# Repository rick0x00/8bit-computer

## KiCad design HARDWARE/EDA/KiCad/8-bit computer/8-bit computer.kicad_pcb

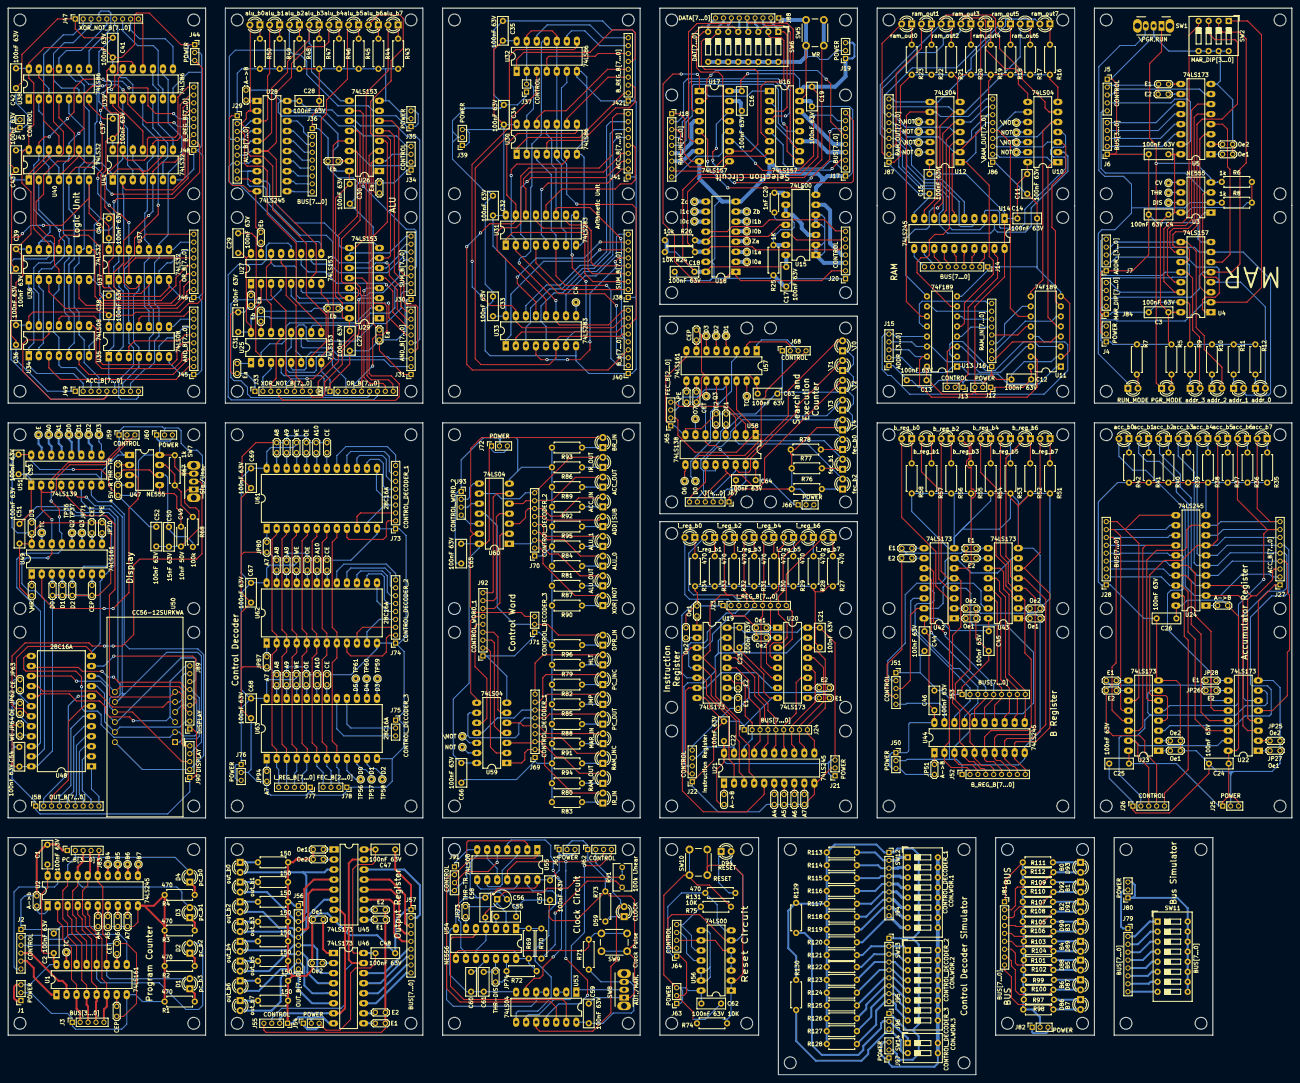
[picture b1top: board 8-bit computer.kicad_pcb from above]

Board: 2 copper layers, 325.0 x 270.0 mm, 601 parts (0 on the bottom side), 106 nets.

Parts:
C1, C2, C3, C4, C5, C11, C12, C13, C14, C15, C16, C17, C18, C19, C21, C22, C23, C24, C25, C26, C27, C28, C29, C30, C31, C32, C33, C34, C35, C36, C37, C38, C39, C40, C41, C42, C43, C44, C45, C46, C47, C48, C51, C52, C53, C54, C57, C58, C59, C62, C63, C64, C65, C66, C67, C68, C69: 100nF 63V; C_Rect_L7.0mm_W2.5mm_P5.00mm
C20: 1nF; C_Disc_D4.3mm_W1.9mm_P5.00mm
C49: 10nF 50V; C_Disc_D4.3mm_W1.9mm_P5.00mm
C50: 15nF 63V; C_Rect_L7.0mm_W2.5mm_P5.00mm
C55, C60: 10nF 63V; C_Rect_L7.0mm_W2.5mm_P5.00mm
C56: 10uF 25V; CP_Radial_Tantal_D4.5mm_P2.50mm
C61: 330nF 63V; C_Rect_L7.0mm_W2.5mm_P5.00mm
D1: pc_b3; LED_D3.0mm
D2: pc_b2; LED_D3.0mm
D3: pc_b1; LED_D3.0mm
D4: pc_b0; LED_D3.0mm
D5: PGR_MODE; LED_D3.0mm
D6: RUN_MODE; LED_D3.0mm
D7: addr_3; LED_D3.0mm
D8: addr_2; LED_D3.0mm
D9: addr_1; LED_D3.0mm
D10: addr_0; LED_D3.0mm
D11: ram_out7; LED_D3.0mm
D12: ram_out6; LED_D3.0mm
D13: ram_out5; LED_D3.0mm
D14: ram_out4; LED_D3.0mm
D15: ram_out3; LED_D3.0mm
D16: ram_out2; LED_D3.0mm
D17: ram_out1; LED_D3.0mm
D18: ram_out0; LED_D3.0mm
D19: i_reg_b7; LED_D3.0mm
D20: i_reg_b6; LED_D3.0mm
D21: i_reg_b5; LED_D3.0mm
D22: i_reg_b4; LED_D3.0mm
D23: i_reg_b3; LED_D3.0mm
D24: i_reg_b2; LED_D3.0mm
D25: i_reg_b1; LED_D3.0mm
D26: i_reg_b0; LED_D3.0mm
D27: acc_b7; LED_D3.0mm
D28: acc_b6; LED_D3.0mm
D29: acc_b5; LED_D3.0mm
D30: acc_b4; LED_D3.0mm
D31: acc_b3; LED_D3.0mm
D32: acc_b2; LED_D3.0mm
D33: acc_b1; LED_D3.0mm
D34: acc_b0; LED_D3.0mm
D35: alu_b7; LED_D3.0mm
D36: alu_b6; LED_D3.0mm
D37: alu_b5; LED_D3.0mm
D38: alu_b4; LED_D3.0mm
D39: alu_b3; LED_D3.0mm
D40: alu_b2; LED_D3.0mm
D41: alu_b1; LED_D3.0mm
D42: alu_b0; LED_D3.0mm
D43: b_reg_b7; LED_D3.0mm
D44: b_reg_b6; LED_D3.0mm
D45: b_reg_b5; LED_D3.0mm
D46: b_reg_b4; LED_D3.0mm
D47: b_reg_b3; LED_D3.0mm
D48: b_reg_b2; LED_D3.0mm
D49: b_reg_b1; LED_D3.0mm
D50: b_reg_b0; LED_D3.0mm
D51: out_b7; LED_D3.0mm_Clear
D52: out_b6; LED_D3.0mm_Clear
D53: out_b5; LED_D3.0mm_Clear
D54: out_b4; LED_D3.0mm_Clear
D55: out_b3; LED_D3.0mm_Clear
D56: out_b2; LED_D3.0mm_Clear
D57: out_b1; LED_D3.0mm_Clear
D58: out_b0; LED_D3.0mm_Clear
D59: CLOCK; LED_D3.0mm
D60: fec_b2; LED_D3.0mm_Clear
D61: fec_b1; LED_D3.0mm_Clear
D62: fec_b0; LED_D3.0mm_Clear
D63: \T4; LED_D3.0mm_Clear
D64: \T3; LED_D3.0mm_Clear
D65: \T2; LED_D3.0mm_Clear
D66: \T1; LED_D3.0mm_Clear
D67: \T0; LED_D3.0mm_Clear
D68: HLT; LED_D3.0mm_Clear
D69: RAM_OUT; LED_D3.0mm_Clear
D70: ALU_0; LED_D3.0mm_Clear
D71: PC_INC; LED_D3.0mm_Clear
D72: IR_IN; LED_D3.0mm_Clear
D73: ALU_1; LED_D3.0mm_Clear
D74: JMP; LED_D3.0mm_Clear
D75: IR_OUT; LED_D3.0mm_Clear
D76: ALU_OUT; LED_D3.0mm_Clear
D77: PC_OUT; LED_D3.0mm_Clear
D78: ACC_OUT; LED_D3.0mm_Clear
D79: XOR|NOT; LED_D3.0mm_Clear
D80: MAR_IN; LED_D3.0mm_Clear
D81: ACC_IN; LED_D3.0mm_Clear
D82: BR_IN; LED_D3.0mm_Clear
D83: RAM_INC; LED_D3.0mm_Clear
D84: ADD|SUB; LED_D3.0mm_Clear
D85: OPR_IN; LED_D3.0mm_Clear
D86: B7; LED_D3.0mm_Clear
D87: B6; LED_D3.0mm_Clear
D88: B5; LED_D3.0mm_Clear
D89: B4; LED_D3.0mm_Clear
D90: B3; LED_D3.0mm_Clear
D91: B2; LED_D3.0mm_Clear
D92: B1; LED_D3.0mm_Clear
D93: B0; LED_D3.0mm_Clear
D94: RESET; LED_D3.0mm
J1, J4, J12, J19, J21, J25, J35, J39, J44, J50, J54, J60, J61, J63, J66, J72, J76, J80, J82, J97: POWER; PinSocket_1x03_P2.00mm_Vertical
J2: CONTROL; PinSocket_1x06_P2.00mm_Vertical
J3, J6: BUS[3...0]; PinSocket_1x05_P2.00mm_Vertical
J5, J22, J26, J51, J64: CONTROL; PinSocket_1x05_P2.00mm_Vertical
J7, J15: ADDR_[3...0]; PinSocket_1x05_P2.00mm_Vertical
J13, J59: CONTROL; PinSocket_1x03_P2.00mm_Vertical
J14, J17, J24, J28, J36, J53, J57, J79, J81: BUS[7...0]; PinSocket_1x09_P2.00mm_Vertical
J16, J18: RAM_IN[7...0]; PinSocket_1x09_P2.00mm_Vertical
J20: CONTROL; PinSocket_1x07_P2.00mm_Vertical
J23: I_REG_B[7...0]; PinSocket_1x09_P2.00mm_Vertical
J27, J41, J49: ACC_B[7...0]; PinSocket_1x09_P2.00mm_Vertical
J29: ALU_B[7...0]; PinSocket_1x09_P2.00mm_Vertical
J30, J38: SUM_B[7...0]; PinSocket_1x09_P2.00mm_Vertical
J31, J45: AND_B[7...0]; PinSocket_1x09_P2.00mm_Vertical
J32, J46: OR_B[7...0]; PinSocket_1x09_P2.00mm_Vertical
J33, J47: XOR_NOT_B[7...0]; PinSocket_1x09_P2.00mm_Vertical
J34, J55, J62, J68, J91: CONTROL; PinSocket_1x04_P2.00mm_Vertical
J37, J43: CONTROL; PinSocket_1x02_P2.00mm_Vertical
J40: B_b[7...0]; PinSocket_1x09_P2.00mm_Vertical
J42, J48, J52: B_REG_B[7...0]; PinSocket_1x09_P2.00mm_Vertical
J56, J58: OUT_B[7...0]; PinSocket_1x09_P2.00mm_Vertical
J65, J78: FEC_B[2...0]; PinSocket_1x04_P2.00mm_Vertical
J67: \T[4...0]; PinSocket_1x06_P2.00mm_Vertical
J69, J73, J94: CONTROL_DECODER_1; PinSocket_1x09_P2.00mm_Vertical
J70, J74, J95: CONTROL_DECODER_2; PinSocket_1x09_P2.00mm_Vertical
J71, J75, J96: CONTROL_DECODER_3; PinSocket_1x03_P2.00mm_Vertical
J77: I_REG_B[7...0]; PinSocket_1x05_P2.00mm_Vertical
J83: PC_B[3...0]; PinSocket_1x05_P2.00mm_Vertical
J84: MAR_DIP[7...0]; PinSocket_1x05_P2.00mm_Vertical
J86: \RAM_OUT[7...0]; PinSocket_1x09_P2.00mm_Vertical
J87: RAM_OUT[7...0]; PinSocket_1x09_P2.00mm_Vertical
J88: DATA[7...0]; PinSocket_1x09_P2.00mm_Vertical
J89: DISPLAY; PinSocket_1x09_P2.00mm_Vertical
J90: DISPLAY; PinSocket_1x05_P2.00mm_Vertical
J92: CONTROL_WORD_1; PinSocket_1x09_P2.00mm_Vertical
J93: CONTROL_WORD_2; PinSocket_1x04_P2.00mm_Vertical
JP1, JP20: A4; TestPoint_2Pads_Pitch2.54mm_Drill0.8mm
JP2, JP21: A5; TestPoint_2Pads_Pitch2.54mm_Drill0.8mm
JP3, JP22: A6; TestPoint_2Pads_Pitch2.54mm_Drill0.8mm
JP4, JP23, JP80, JP87, JP94: A7; TestPoint_2Pads_Pitch2.54mm_Drill0.8mm
JP5: A->b; TestPoint_2Pads_Pitch2.54mm_Drill0.8mm
JP6, JP71, JP77: CET; TestPoint_2Pads_Pitch2.54mm_Drill0.8mm
JP7, JP67, JP75: CEP; TestPoint_2Pads_Pitch2.54mm_Drill0.8mm
JP8, JP14, JP18, JP27, JP31, JP45, JP49, JP56, JP58: Oe1; TestPoint_2Pads_Pitch2.54mm_Drill0.8mm
JP9, JP13, JP17, JP26, JP30, JP44, JP48, JP53, JP55, JP78: E2; TestPoint_2Pads_Pitch2.54mm_Drill0.8mm
JP10, JP12, JP16, JP25, JP29, JP43, JP47, JP52, JP54: Oe2; TestPoint_2Pads_Pitch2.54mm_Drill0.8mm
JP11, JP15, JP19, JP28, JP32, JP46, JP50, JP57, JP59, JP79: E1; TestPoint_2Pads_Pitch2.54mm_Drill0.8mm
JP24, JP33, JP40, JP51: A->B; TestPoint_2Pads_Pitch2.54mm_Drill0.8mm
JP34, JP36, JP38, JP41: Ea; TestPoint_2Pads_Pitch2.54mm_Drill0.8mm
JP35, JP37, JP39, JP42: Eb; TestPoint_2Pads_Pitch2.54mm_Drill0.8mm
JP60: +5V-R; TestPoint_2Pads_Pitch2.54mm_Drill0.8mm
JP61, JP73: THR-TR; TestPoint_2Pads_Pitch2.54mm_Drill0.8mm
JP62, JP85, JP92, JP99: OE; TestPoint_2Pads_Pitch2.54mm_Drill0.8mm
JP63, JP84, JP91, JP98: CE; TestPoint_2Pads_Pitch2.54mm_Drill0.8mm
JP64, JP86, JP93, JP100: WE; TestPoint_2Pads_Pitch2.54mm_Drill0.8mm
JP65: D0; TestPoint_2Pads_Pitch2.54mm_Drill0.8mm
JP66: D2; TestPoint_2Pads_Pitch2.54mm_Drill0.8mm
JP68: D1; TestPoint_2Pads_Pitch2.54mm_Drill0.8mm
JP69: D3; TestPoint_2Pads_Pitch2.54mm_Drill0.8mm
JP70, JP76: \PE; TestPoint_2Pads_Pitch2.54mm_Drill0.8mm
JP72: \MR; TestPoint_2Pads_Pitch2.54mm_Drill0.8mm
JP74: THR-DIS; TestPoint_2Pads_Pitch2.54mm_Drill0.8mm
JP81, JP88, JP95: A8; TestPoint_2Pads_Pitch2.54mm_Drill0.8mm
JP82, JP89, JP96: A9; TestPoint_2Pads_Pitch2.54mm_Drill0.8mm
JP83, JP90, JP97: A10; TestPoint_2Pads_Pitch2.54mm_Drill0.8mm
R1, R2, R3, R4, R5, R7, R16, R17, R18, R19, R20, R21, R22, R23, R27, R28, R29, R30, R31, R32, R33, R34, R35, R36, R37, R38, R39, R40, R41, R42, R43, R44, R45, R46, R47, R48, R49, R50, R51, R52, R53, R54, R55, R56, R57, R58, R73, R131: 470; R_Axial_DIN0207_L6.3mm_D2.5mm_P7.62mm_Horizontal
R6, R8, R67: 1k; R_Axial_DIN0207_L6.3mm_D2.5mm_P7.62mm_Horizontal
R9, R10, R11, R12, R59, R60, R61, R62, R63, R64, R65, R66, R69: 150; R_Axial_DIN0207_L6.3mm_D2.5mm_P7.62mm_Horizontal
R24, R74, R75: 10K; R_Axial_DIN0207_L6.3mm_D2.5mm_P7.62mm_Horizontal
R25, R98, R100, R102, R104, R106, R108, R110, R112: 1K; R_Axial_DIN0207_L6.3mm_D2.5mm_P7.62mm_Horizontal
R26, R71, R97, R99, R101, R103, R105, R107, R109, R111, R113, R114, R115, R116, R117, R118, R119, R120, R121, R122, R123, R124, R125, R126, R127, R128, R129, R130: 10k; R_Axial_DIN0207_L6.3mm_D2.5mm_P7.62mm_Horizontal
R68: 100k; R_Axial_DIN0207_L6.3mm_D2.5mm_P7.62mm_Horizontal
R70: 10; R_Axial_DIN0207_L6.3mm_D2.5mm_P7.62mm_Horizontal
R72: 330k; R_Axial_DIN0207_L6.3mm_D2.5mm_P7.62mm_Horizontal
R76, R77, R78: 330; R_Axial_DIN0207_L6.3mm_D2.5mm_P7.62mm_Horizontal
R79, R80, R81, R82, R83, R84, R85, R86, R87, R88, R89, R90, R91, R92, R93, R94, R95, R96: 3K; R_Axial_DIN0207_L6.3mm_D2.5mm_P7.62mm_Horizontal
RV1: 100k Linear; Potentiometer_Bourns_3266Y_Vertical
SW1: \PGR,RUN; SW_CuK_OS102011MA1QN1_SPDT_Angled
SW2: MAR_DIP[3...0]; SW_DIP_SPSTx04_Slide_9.78x12.34mm_W7.62mm_P2.54mm
SW5: WR; SW_PUSH_6mm_H5mm
SW6: DAT[7...0]; SW_DIP_SPSTx08_Slide_9.78x22.5mm_W7.62mm_P2.54mm
SW7: Sig./Uns.; SW_CuK_OS102011MA1QN1_SPDT_Angled
SW8: AUT./MAN.; SW_CuK_OS102011MA1QN1_SPDT_Angled
SW9: Clock Pulse; SW_PUSH_6mm_H5mm
SW10: RESET; SW_PUSH_6mm_H5mm
SW11: BUS[7...0]; SW_DIP_SPSTx08_Slide_9.78x22.5mm_W7.62mm_P2.54mm
SW12: CON.WOR.1; SW_DIP_SPSTx08_Slide_9.78x22.5mm_W7.62mm_P2.54mm
SW13: CON.WOR.2; SW_DIP_SPSTx08_Slide_9.78x22.5mm_W7.62mm_P2.54mm
SW14: CON.WOR.3; SW_DIP_SPSTx02_Slide_9.78x7.26mm_W7.62mm_P2.54mm
TP1: B4; TestPoint_THTPad_D1.5mm_Drill0.7mm
TP2: B5; TestPoint_THTPad_D1.5mm_Drill0.7mm
TP3: B6; TestPoint_THTPad_D1.5mm_Drill0.7mm
TP4: B7; TestPoint_THTPad_D1.5mm_Drill0.7mm
TP5, TP38, TP51: TC; TestPoint_THTPad_D1.5mm_Drill0.7mm
TP6: CV; TestPoint_THTPad_D1.5mm_Drill0.7mm
TP7: DIS; TestPoint_THTPad_D1.5mm_Drill0.7mm
TP8: THR; TestPoint_THTPad_D1.5mm_Drill0.7mm
TP18, TP19, TP22, TP23, TP54: NOT; TestPoint_THTPad_D1.5mm_Drill0.7mm
TP20, TP21, TP24, TP25, TP55: \NOT; TestPoint_THTPad_D1.5mm_Drill0.7mm
TP26: I0a; TestPoint_THTPad_D1.5mm_Drill0.7mm
TP27: I1a; TestPoint_THTPad_D1.5mm_Drill0.7mm
TP28: I0b; TestPoint_THTPad_D1.5mm_Drill0.7mm
TP29: I1b; TestPoint_THTPad_D1.5mm_Drill0.7mm
TP30: I0c; TestPoint_THTPad_D1.5mm_Drill0.7mm
TP31: I1c; TestPoint_THTPad_D1.5mm_Drill0.7mm
TP32: Za; TestPoint_THTPad_D1.5mm_Drill0.7mm
TP33: Zb; TestPoint_THTPad_D1.5mm_Drill0.7mm
TP34: Zc; TestPoint_THTPad_D1.5mm_Drill0.7mm
TP35: C4; TestPoint_THTPad_D1.5mm_Drill0.7mm
TP36: Q2; TestPoint_THTPad_D1.5mm_Drill0.7mm
TP37, TP50: Q3; TestPoint_THTPad_D1.5mm_Drill0.7mm
TP39: A1; TestPoint_THTPad_D1.5mm_Drill0.7mm
TP40: A0; TestPoint_THTPad_D1.5mm_Drill0.7mm
TP41: E; TestPoint_THTPad_D1.5mm_Drill0.7mm
TP42: O0; TestPoint_THTPad_D1.5mm_Drill0.7mm
TP43: O1; TestPoint_THTPad_D1.5mm_Drill0.7mm
TP44: O2; TestPoint_THTPad_D1.5mm_Drill0.7mm
TP45: O3; TestPoint_THTPad_D1.5mm_Drill0.7mm
TP46, TP56: D0; TestPoint_THTPad_D1.5mm_Drill0.7mm
TP47, TP57: D1; TestPoint_THTPad_D1.5mm_Drill0.7mm
TP48, TP58: D2; TestPoint_THTPad_D1.5mm_Drill0.7mm
TP49, TP59: D3; TestPoint_THTPad_D1.5mm_Drill0.7mm
TP52: O6; TestPoint_THTPad_D1.5mm_Drill0.7mm
TP53: O7; TestPoint_THTPad_D1.5mm_Drill0.7mm
TP60: D4; TestPoint_THTPad_D1.5mm_Drill0.7mm
TP61: D5; TestPoint_THTPad_D1.5mm_Drill0.7mm
U1, U49, U57: 74LS161; DIP-16_W7.62mm_LongPads
U2, U14, U21, U24, U28, U44: 74LS245; DIP-20_W7.62mm_LongPads
U3, U47: NE555; DIP-8_W7.62mm_LongPads
U4, U16, U17, U18: 74LS157; DIP-16_W7.62mm_LongPads
U5, U19, U20, U22, U23, U42, U43, U45, U46: 74LS173; DIP-16_W7.62mm_LongPads
U10, U12, U53, U59, U60: 74LS04; DIP-14_W7.62mm_LongPads
U11, U13: 74F189; DIP-16_W7.62mm
U15, U55, U56: 74LS00; DIP-14_W7.62mm_LongPads
U25, U26, U27, U29: 74LS153; DIP-16_W7.62mm_LongPads
U30, U32, U38, U39: 74LS86; DIP-14_W7.62mm_LongPads
U31, U33: 74LS283; DIP-16_W7.62mm_LongPads
U34, U35: 74LS08; DIP-14_W7.62mm_LongPads
U36, U37, U40, U41: 74LS32; DIP-14_W7.62mm_LongPads
U48, U61, U62, U63: 28C16A; DIP-24_W15.24mm_LongPads
U50: CC56-12SURKWA; CA56-12SURKWA
U51: 74LS139; DIP-16_W7.62mm_LongPads
U54: NE556; DIP-14_W7.62mm_LongPads
U58: 74LS138; DIP-16_W7.62mm_LongPads

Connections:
+5V: C11.1, C12.1, C13.1, C14.1, C15.1, C51.1, C52.1, C53.1, C54.1, J12.1, J12.3, J60.1, J60.3, JP60.2, JP64.1, JP65.1, JP66.1, JP67.1, JP68.1, JP69.1, JP70.1, JP71.1, JP72.1, R67.1, SW7.3, U10.14, U11.16, U12.14, U13.16, U14.1, U14.20, U47.8, U48.24, U49.16, U51.16
/\ram_out0: J86.2, U10.1, U11.5
/\ram_out1: J86.3, U10.3, U11.7
/\ram_out2: J86.4, U10.5, U11.9
/\ram_out3: J86.5, U10.9, U11.11
/\ram_out4: J86.6, U12.1, U13.5
/\ram_out5: J86.7, U12.3, U13.7
/\ram_out6: J86.8, U12.5, U13.9
/\ram_out7: J86.9, U12.9, U13.11
/display_seg_a: J89.2, U48.9, U50.11
/display_seg_b: J89.3, U48.10, U50.7
/display_seg_c: J89.4, U48.11, U50.4
/display_seg_d: J89.5, U48.13, U50.2
/display_seg_dpx: J89.9, U48.17, U50.3
/display_seg_e: J89.6, U48.14, U50.1
/display_seg_f: J89.7, U48.15, U50.10
/display_seg_g: J89.8, U48.16, U50.5
/dp1: J90.2, U50.12, U51.7
/dp2: J90.3, U50.9, U51.6
/dp3: J90.4, U50.8, U51.5
/dp4: J90.5, U50.6, U51.4
/ram_out0: D18.2, J87.2, U10.2, U14.2
/ram_out1: D17.2, J87.3, U10.4, U14.3
/ram_out2: D16.2, J87.4, U10.6, U14.4
/ram_out3: D15.2, J87.5, U10.8, U14.5
/ram_out4: D14.2, J87.6, U12.2, U14.6
/ram_out5: D13.2, J87.7, U12.4, U14.7
/ram_out6: D12.2, J87.8, U12.6, U14.8
/ram_out7: D11.2, J87.9, U12.8, U14.9
GND: C11.2, C12.2, C13.2, C14.2, C15.2, C49.2, C50.2, C51.2, C52.2, C53.2, C54.2, J12.2, J13.1, J14.1, J15.1, J16.1, J58.1, J59.1, J60.2, J86.1, J87.1, J89.1, J90.1, JP62.1, JP63.1, R16.2, R17.2, R18.2, R19.2, R20.2, R21.2, R22.2, R23.2, SW7.1, U10.7, U11.2, U11.8, U12.7, U13.2, U13.8, U14.10, U47.1, U48.12, U49.8, U51.1, U51.8
unnamed: C49.1, U47.5
unnamed: C50.1, JP61.2, R68.2, U47.6
unnamed: D11.1, R16.1
unnamed: D12.1, R17.1
unnamed: D13.1, R18.1
unnamed: D14.1, R19.1
unnamed: D15.1, R20.1
unnamed: D16.1, R21.1
unnamed: D17.1, R22.1
unnamed: D18.1, R23.1
unnamed: JP60.1, U47.4
unnamed: JP61.1, U47.2
unnamed: JP62.2, U48.20
unnamed: JP63.2, U48.18
unnamed: JP64.2, U48.21
unnamed: JP65.2, U49.3
unnamed: JP66.2, U49.5
unnamed: JP67.2, U49.7
unnamed: JP68.2, U49.4
unnamed: JP69.2, U49.6
unnamed: JP70.2, U49.9
unnamed: JP71.2, U49.10
unnamed: JP72.2, U49.1
unnamed: R67.2, R68.1, U47.7
unnamed: SW7.2, U48.19
unnamed: TP18.1, U10.11
unnamed: TP19.1, U10.13
unnamed: TP20.1, U10.10
unnamed: TP21.1, U10.12
unnamed: TP22.1, U12.11
unnamed: TP23.1, U12.13
unnamed: TP24.1, U12.10
unnamed: TP25.1, U12.12
unnamed: TP36.1, U49.12
unnamed: TP37.1, U49.11
unnamed: TP38.1, U49.15
unnamed: TP39.1, U51.13
unnamed: TP40.1, U51.14
unnamed: TP41.1, U51.15
unnamed: TP42.1, U51.12
unnamed: TP43.1, U51.11
unnamed: TP44.1, U51.10
unnamed: TP45.1, U51.9
unnamed: U47.3, U49.2
\RAM_OUT: J13.2, U14.19
\WE: J13.3, U11.3, U13.3
addr_0: J15.2, U11.1, U13.1
addr_1: J15.3, U11.15, U13.15
addr_2: J15.4, U11.14, U13.14
addr_3: J15.5, U11.13, U13.13
bus0: J14.2, U14.18
bus1: J14.3, U14.17
bus2: J14.4, U14.16
bus3: J14.5, U14.15
bus4: J14.6, U14.14
bus5: J14.7, U14.13
bus6: J14.8, U14.12
bus7: J14.9, U14.11
ctnH: J59.2, U48.22, U49.13, U51.3
ctnL: J59.3, U48.23, U49.14, U51.2
out_b0: J58.2, U48.8
out_b1: J58.3, U48.7
out_b2: J58.4, U48.6
out_b3: J58.5, U48.5
out_b4: J58.6, U48.4
out_b5: J58.7, U48.3
out_b6: J58.8, U48.2
out_b7: J58.9, U48.1
ram_in0: J16.2, U11.4
ram_in1: J16.3, U11.6
ram_in2: J16.4, U11.10
ram_in3: J16.5, U11.12
ram_in4: J16.6, U13.4
ram_in5: J16.7, U13.6
ram_in6: J16.8, U13.10
ram_in7: J16.9, U13.12

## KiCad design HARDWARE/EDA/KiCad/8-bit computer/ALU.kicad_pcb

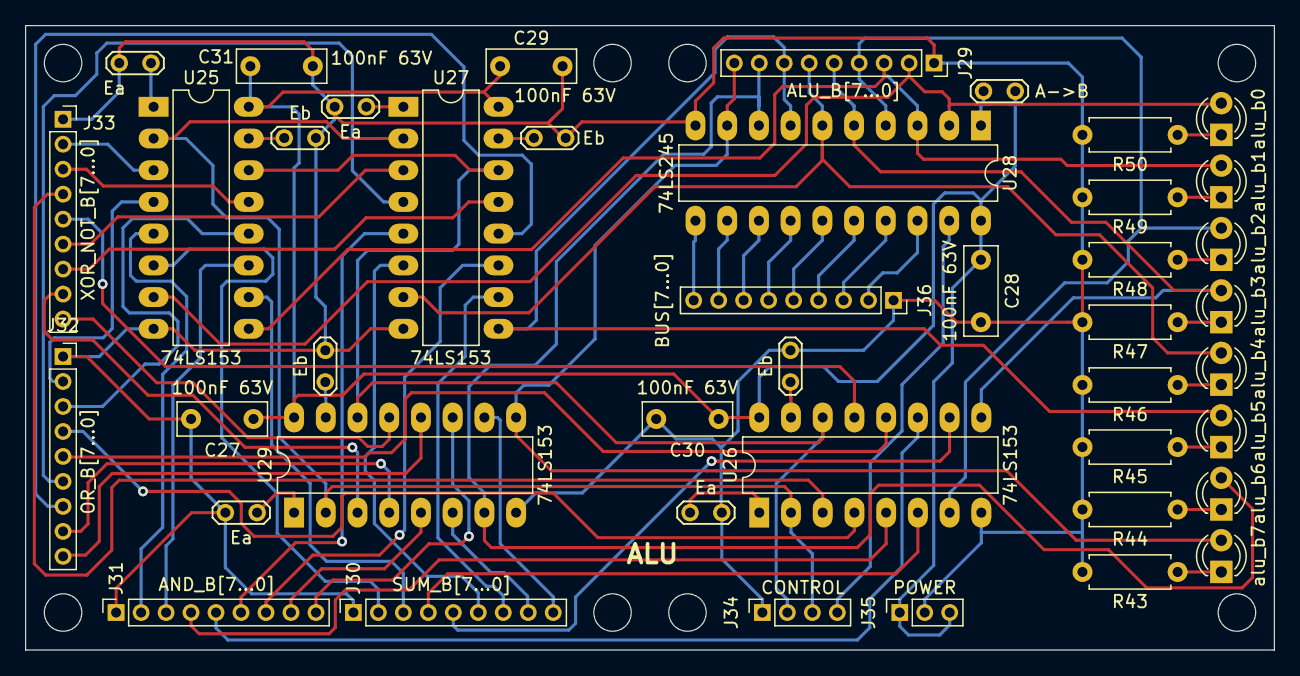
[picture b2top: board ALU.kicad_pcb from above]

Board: 2 copper layers, 100.0 x 50.0 mm, 43 parts (0 on the bottom side), 70 nets.

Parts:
C27, C28, C29, C30, C31: 100nF 63V; C_Rect_L7.0mm_W2.5mm_P5.00mm
D35: alu_b7; LED_D3.0mm
D36: alu_b6; LED_D3.0mm
D37: alu_b5; LED_D3.0mm
D38: alu_b4; LED_D3.0mm
D39: alu_b3; LED_D3.0mm
D40: alu_b2; LED_D3.0mm
D41: alu_b1; LED_D3.0mm
D42: alu_b0; LED_D3.0mm
J29: ALU_B[7...0]; PinSocket_1x09_P2.00mm_Vertical
J30: SUM_B[7...0]; PinSocket_1x09_P2.00mm_Vertical
J31: AND_B[7...0]; PinSocket_1x09_P2.00mm_Vertical
J32: OR_B[7...0]; PinSocket_1x09_P2.00mm_Vertical
J33: XOR_NOT_B[7...0]; PinSocket_1x09_P2.00mm_Vertical
J34: CONTROL; PinSocket_1x04_P2.00mm_Vertical
J35: POWER; PinSocket_1x03_P2.00mm_Vertical
J36: BUS[7...0]; PinSocket_1x09_P2.00mm_Vertical
JP34, JP36, JP38, JP41: Ea; TestPoint_2Pads_Pitch2.54mm_Drill0.8mm
JP35, JP37, JP39, JP42: Eb; TestPoint_2Pads_Pitch2.54mm_Drill0.8mm
JP40: A->B; TestPoint_2Pads_Pitch2.54mm_Drill0.8mm
R43, R44, R45, R46, R47, R48, R49, R50: 470; R_Axial_DIN0207_L6.3mm_D2.5mm_P7.62mm_Horizontal
U25, U26, U27, U29: 74LS153; DIP-16_W7.62mm_LongPads
U28: 74LS245; DIP-20_W7.62mm_LongPads

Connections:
+5V: C27.1, C28.1, C29.1, C30.1, C31.1, J35.1, J35.3, JP40.1, U25.16, U26.16, U27.16, U28.20, U29.16
ALU_0: J34.2, U25.14, U26.14, U27.14, U29.14
ALU_1: J34.3, U25.2, U26.2, U27.2, U29.2
GND: C27.2, C28.2, C29.2, C30.2, C31.2, J29.1, J30.1, J31.1, J32.1, J33.1, J34.1, J35.2, J36.1, JP34.1, JP35.1, JP36.1, JP37.1, JP38.1, JP39.1, JP41.1, JP42.1, R43.2, R44.2, R45.2, R46.2, R47.2, R48.2, R49.2, R50.2, U25.8, U26.8, U27.8, U28.10, U29.8
unnamed: D35.1, R43.1
unnamed: D36.1, R44.1
unnamed: D37.1, R45.1
unnamed: D38.1, R46.1
unnamed: D39.1, R47.1
unnamed: D40.1, R48.1
unnamed: D41.1, R49.1
unnamed: D42.1, R50.1
unnamed: JP34.2, U25.1
unnamed: JP35.2, U25.15
unnamed: JP36.2, U26.1
unnamed: JP37.2, U26.15
unnamed: JP38.2, U27.1
unnamed: JP39.2, U27.15
unnamed: JP40.2, U28.1
unnamed: JP41.2, U29.1
unnamed: JP42.2, U29.15
\ALU_OUT: J34.4, U28.19
alu_b0: D42.2, J29.2, U25.7, U28.2
alu_b1: D41.2, J29.3, U25.9, U28.3
alu_b2: D40.2, J29.4, U26.7, U28.4
alu_b3: D39.2, J29.5, U26.9, U28.5
alu_b4: D38.2, J29.6, U27.7, U28.6
alu_b5: D37.2, J29.7, U27.9, U28.7
alu_b6: D36.2, J29.8, U28.8, U29.7
alu_b7: D35.2, J29.9, U28.9, U29.9
and_b0: J31.2, U25.5
and_b1: J31.3, U25.11
and_b2: J31.4, U26.5
and_b3: J31.5, U26.11
and_b4: J31.6, U27.5
and_b5: J31.7, U27.11
and_b6: J31.8, U29.5
and_b7: J31.9, U29.11
bus0: J36.2, U28.18
bus1: J36.3, U28.17
bus2: J36.4, U28.16
bus3: J36.5, U28.15
bus4: J36.6, U28.14
bus5: J36.7, U28.13
bus6: J36.8, U28.12
bus7: J36.9, U28.11
or_b0: J32.2, U25.4
or_b1: J32.3, U25.12
or_b2: J32.4, U26.4
or_b3: J32.5, U26.12
or_b4: J32.6, U27.4
or_b5: J32.7, U27.12
or_b6: J32.8, U29.4
or_b7: J32.9, U29.12
sum_b0: J30.2, U25.6
sum_b1: J30.3, U25.10
sum_b2: J30.4, U26.6
sum_b3: J30.5, U26.10
sum_b4: J30.6, U27.6
sum_b5: J30.7, U27.10
sum_b6: J30.8, U29.6
sum_b7: J30.9, U29.10
xor_not_b0: J33.2, U25.3
xor_not_b1: J33.3, U25.13
xor_not_b2: J33.4, U26.3
xor_not_b3: J33.5, U26.13
xor_not_b4: J33.6, U27.3
xor_not_b5: J33.7, U27.13
xor_not_b6: J33.8, U29.3
xor_not_b7: J33.9, U29.13

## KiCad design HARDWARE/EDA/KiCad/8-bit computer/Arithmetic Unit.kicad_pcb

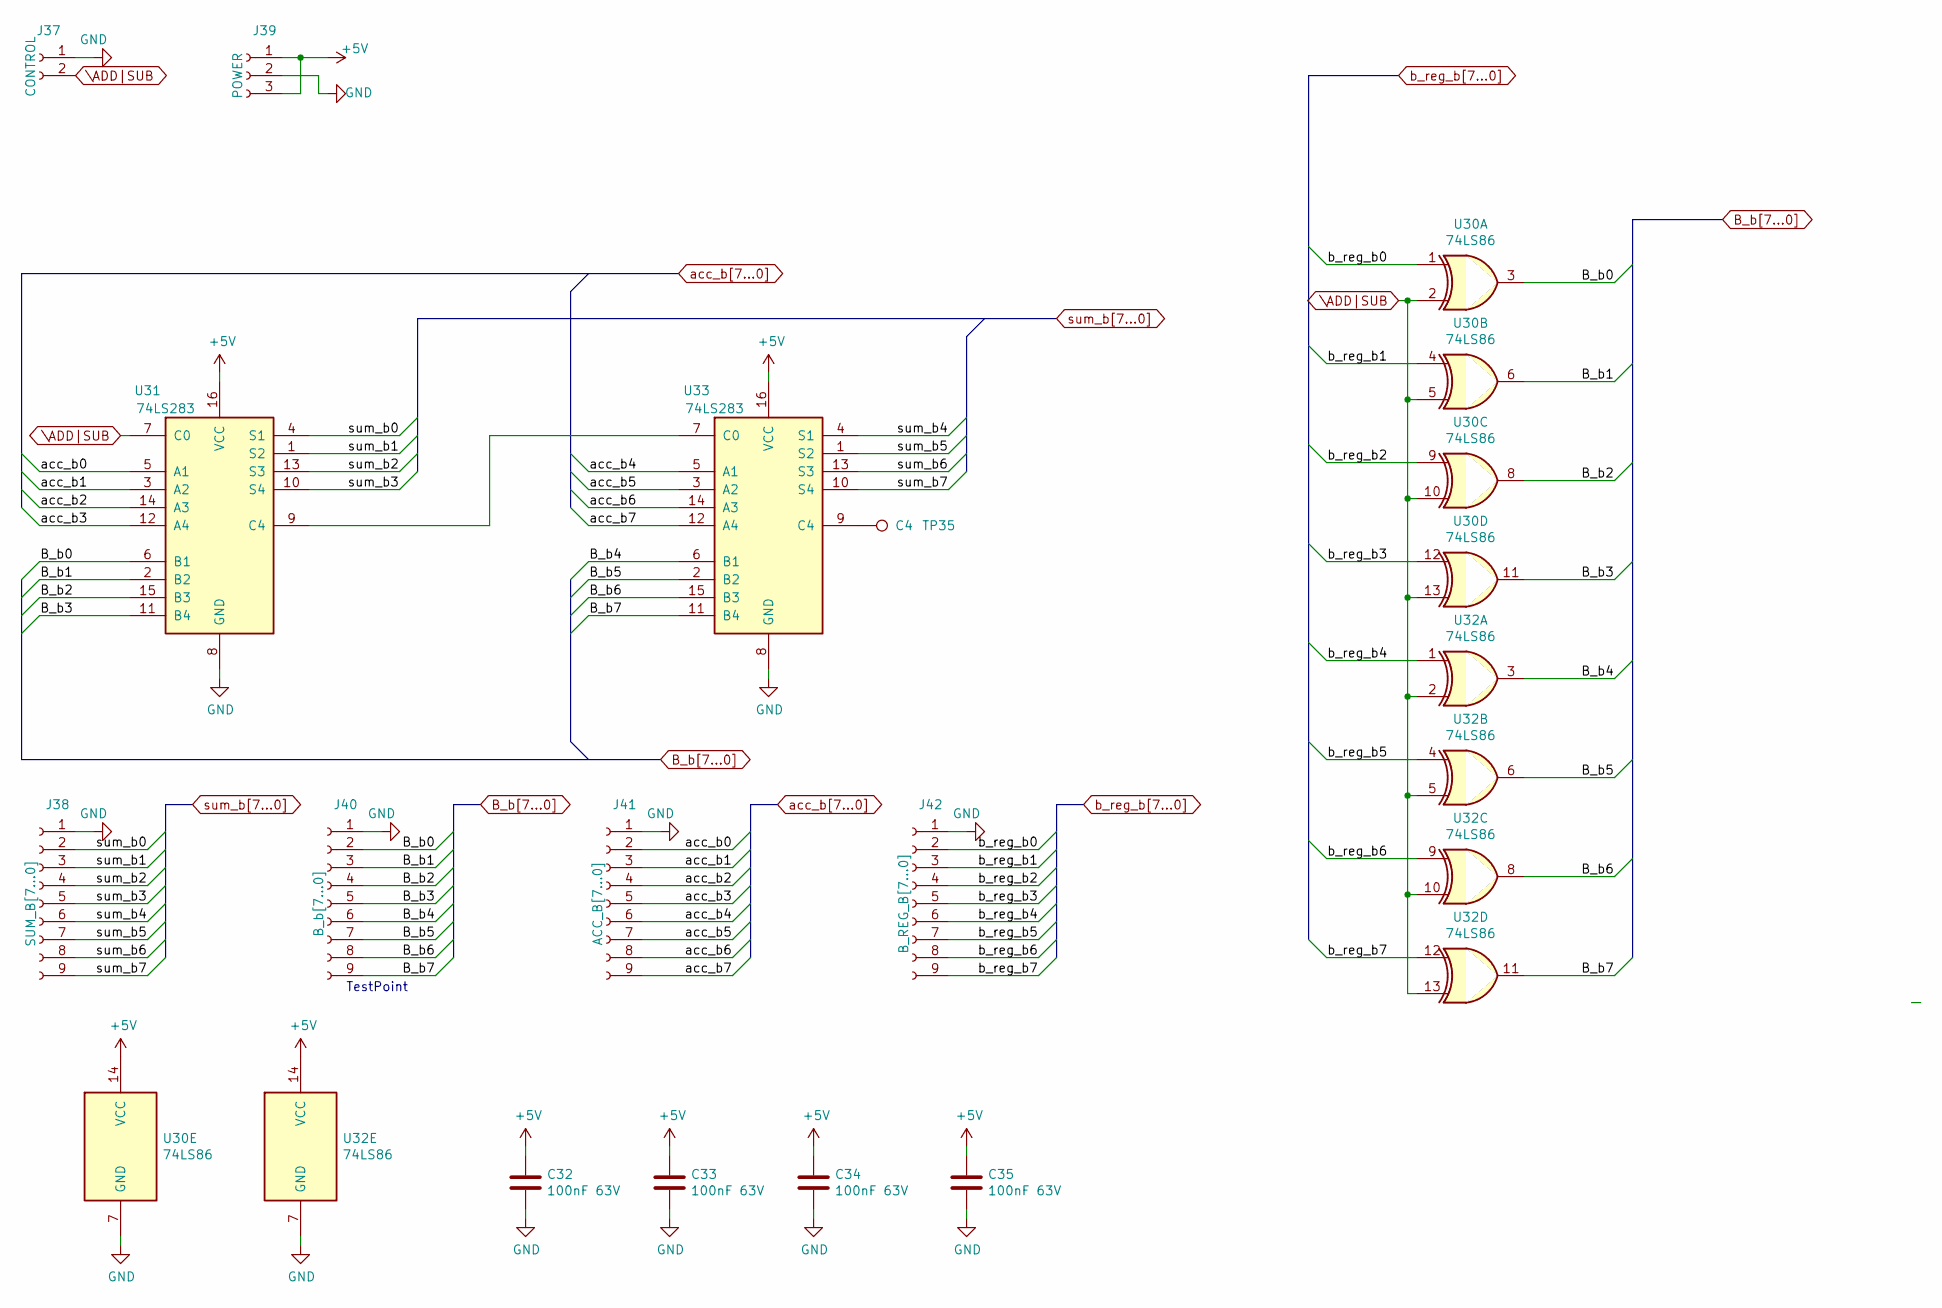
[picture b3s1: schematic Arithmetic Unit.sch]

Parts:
C32, C33, C34, C35: 100nF 63V; C_Rect_L7.0mm_W2.5mm_P5.00mm
J37: CONTROL; PinSocket_1x02_P2.00mm_Vertical
J38: SUM_B[7...0]; PinSocket_1x09_P2.00mm_Vertical
J39: POWER; PinSocket_1x03_P2.00mm_Vertical
J40: B_b[7...0]; PinSocket_1x09_P2.00mm_Vertical
J41: ACC_B[7...0]; PinSocket_1x09_P2.00mm_Vertical
J42: B_REG_B[7...0]; PinSocket_1x09_P2.00mm_Vertical
TP35: C4; TestPoint_THTPad_D1.5mm_Drill0.7mm
U30, U32: 74LS86; DIP-14_W7.62mm_LongPads
U31, U33: 74LS283; DIP-16_W7.62mm_LongPads

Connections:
+5V: C32.1, C33.1, C34.1, C35.1, J39.1, J39.3, U30.14 (VCC), U31.16 (VCC), U32.14 (VCC), U33.16 (VCC)
B_b0: J40.2, U30.3, U31.6 (B1)
B_b1: J40.3, U30.6, U31.2 (B2)
B_b2: J40.4, U30.8, U31.15 (B3)
B_b3: J40.5, U30.11, U31.11 (B4)
B_b4: J40.6, U32.3, U33.6 (B1)
B_b5: J40.7, U32.6, U33.2 (B2)
B_b6: J40.8, U32.8, U33.15 (B3)
B_b7: J40.9, U32.11, U33.11 (B4)
GND: C32.2, C33.2, C34.2, C35.2, J37.1, J38.1, J39.2, J40.1, J41.1, J42.1, U30.7 (GND), U31.8 (GND), U32.7 (GND), U33.8 (GND)
unnamed: TP35.1, U33.9 (C4)
unnamed: U31.9 (C4), U33.7 (C0)
\ADD|SUB: J37.2, U30.2, U30.5, U30.10, U30.13, U31.7 (C0), U32.2, U32.5, U32.10, U32.13
acc_b0: J41.2, U31.5 (A1)
acc_b1: J41.3, U31.3 (A2)
acc_b2: J41.4, U31.14 (A3)
acc_b3: J41.5, U31.12 (A4)
acc_b4: J41.6, U33.5 (A1)
acc_b5: J41.7, U33.3 (A2)
acc_b6: J41.8, U33.14 (A3)
acc_b7: J41.9, U33.12 (A4)
b_reg_b0: J42.2, U30.1
b_reg_b1: J42.3, U30.4
b_reg_b2: J42.4, U30.9
b_reg_b3: J42.5, U30.12
b_reg_b4: J42.6, U32.1
b_reg_b5: J42.7, U32.4
b_reg_b6: J42.8, U32.9
b_reg_b7: J42.9, U32.12
sum_b0: J38.2, U31.4 (S1)
sum_b1: J38.3, U31.1 (S2)
sum_b2: J38.4, U31.13 (S3)
sum_b3: J38.5, U31.10 (S4)
sum_b4: J38.6, U33.4 (S1)
sum_b5: J38.7, U33.1 (S2)
sum_b6: J38.8, U33.13 (S3)
sum_b7: J38.9, U33.10 (S4)

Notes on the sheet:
TestPoint

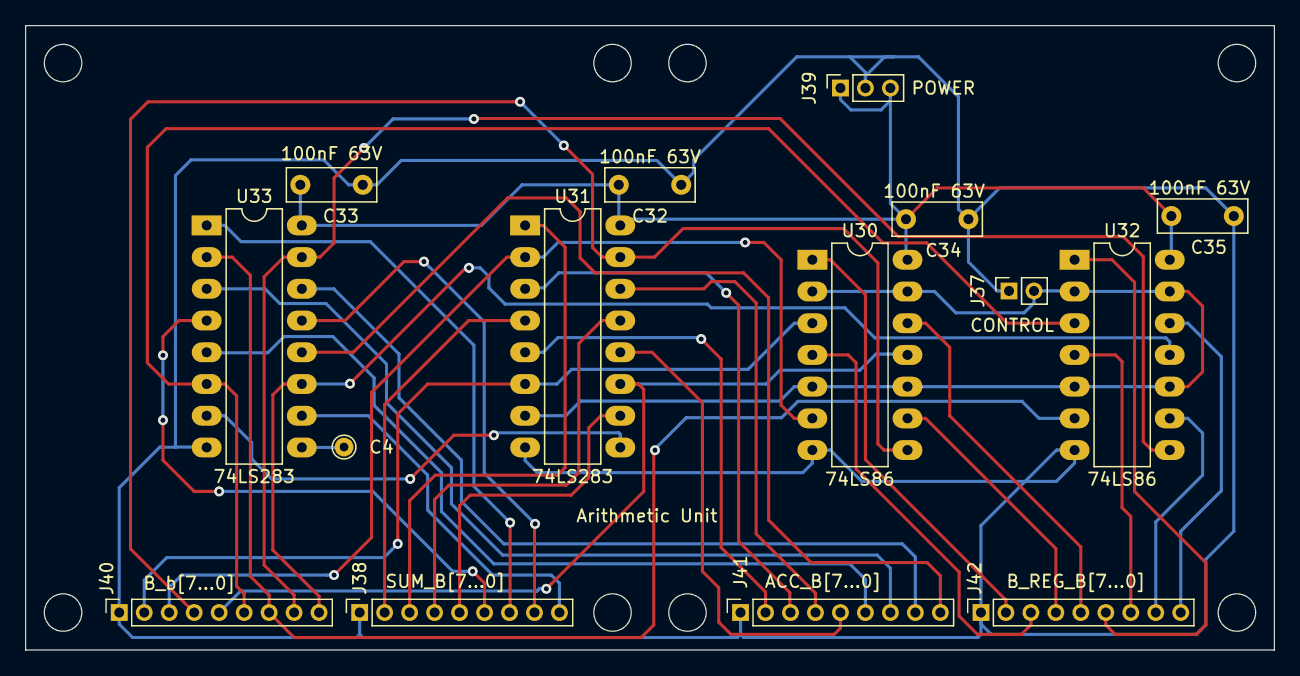
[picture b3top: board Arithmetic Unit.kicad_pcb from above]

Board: 2 copper layers, 100.0 x 50.0 mm, 15 parts (0 on the bottom side), 37 nets.

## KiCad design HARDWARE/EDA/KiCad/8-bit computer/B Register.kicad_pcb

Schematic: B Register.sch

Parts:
C44, C45, C46: 100nF 63V; C_Rect_L7.0mm_W2.5mm_P5.00mm
D43: b_reg_b7; LED_D3.0mm
D44: b_reg_b6; LED_D3.0mm
D45: b_reg_b5; LED_D3.0mm
D46: b_reg_b4; LED_D3.0mm
D47: b_reg_b3; LED_D3.0mm
D48: b_reg_b2; LED_D3.0mm
D49: b_reg_b1; LED_D3.0mm
D50: b_reg_b0; LED_D3.0mm
J50: POWER; PinSocket_1x03_P2.00mm_Vertical
J51: CONTROL; PinSocket_1x05_P2.00mm_Vertical
J52: B_REG_B[7...0]; PinSocket_1x09_P2.00mm_Vertical
J53: BUS[7...0]; PinSocket_1x09_P2.00mm_Vertical
JP43, JP47: Oe2; TestPoint_2Pads_Pitch2.54mm_Drill0.8mm
JP44, JP48: E2; TestPoint_2Pads_Pitch2.54mm_Drill0.8mm
JP45, JP49: Oe1; TestPoint_2Pads_Pitch2.54mm_Drill0.8mm
JP46, JP50: E1; TestPoint_2Pads_Pitch2.54mm_Drill0.8mm
JP51: A->B; TestPoint_2Pads_Pitch2.54mm_Drill0.8mm
R51, R52, R53, R54, R55, R56, R57, R58: 470; R_Axial_DIN0207_L6.3mm_D2.5mm_P7.62mm_Horizontal
U42, U43: 74LS173; DIP-16_W7.62mm_LongPads
U44: 74LS245; DIP-20_W7.62mm_LongPads

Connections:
+5V: C44.1, C45.1, C46.1, J50.1, J50.3, JP51.1 (A), U42.16, U43.16, U44.20 (VCC)
CLOCK: J51.2, U42.7, U43.7
GND: C44.2, C45.2, C46.2, J50.2, J51.1, J52.1, J53.1, JP43.1 (A), JP45.1 (A), JP47.1 (A), JP49.1 (A), R51.2, R52.2, R53.2, R54.2, R55.2, R56.2, R57.2, R58.2, U42.8, U43.8, U44.10 (GND)
unnamed: D43.1 (K), R51.1
unnamed: D44.1 (K), R52.1
unnamed: D45.1 (K), R53.1
unnamed: D46.1 (K), R54.1
unnamed: D47.1 (K), R55.1
unnamed: D48.1 (K), R56.1
unnamed: D49.1 (K), R57.1
unnamed: D50.1 (K), R58.1
unnamed: JP43.2 (B), U42.2
unnamed: JP44.2 (B), U42.10
unnamed: JP45.2 (B), U42.1
unnamed: JP46.2 (B), U42.9
unnamed: JP47.2 (B), U43.2
unnamed: JP48.2 (B), U43.10
unnamed: JP49.2 (B), U43.1
unnamed: JP50.2 (B), U43.9
unnamed: JP51.2 (B), U44.1 (A->B)
RESET: J51.3, U42.15, U43.15
\BR_IN: J51.4, JP44.1 (A), JP46.1 (A), JP48.1 (A), JP50.1 (A)
\BR_OUT: J51.5, U44.19 (CE)
b_reg_b0: D50.2 (A), J52.2, U42.3, U44.2 (A0)
b_reg_b1: D49.2 (A), J52.3, U42.4, U44.3 (A1)
b_reg_b2: D48.2 (A), J52.4, U42.5, U44.4 (A2)
b_reg_b3: D47.2 (A), J52.5, U42.6, U44.5 (A3)
b_reg_b4: D46.2 (A), J52.6, U43.3, U44.6 (A4)
b_reg_b5: D45.2 (A), J52.7, U43.4, U44.7 (A5)
b_reg_b6: D44.2 (A), J52.8, U43.5, U44.8 (A6)
b_reg_b7: D43.2 (A), J52.9, U43.6, U44.9 (A7)
bus0: J53.2, U42.14, U44.18 (B0)
bus1: J53.3, U42.13, U44.17 (B1)
bus2: J53.4, U42.12, U44.16 (B2)
bus3: J53.5, U42.11, U44.15 (B3)
bus4: J53.6, U43.14, U44.14 (B4)
bus5: J53.7, U43.13, U44.13 (B5)
bus6: J53.8, U43.12, U44.12 (B6)
bus7: J53.9, U43.11, U44.11 (B7)

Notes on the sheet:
Red 3mm

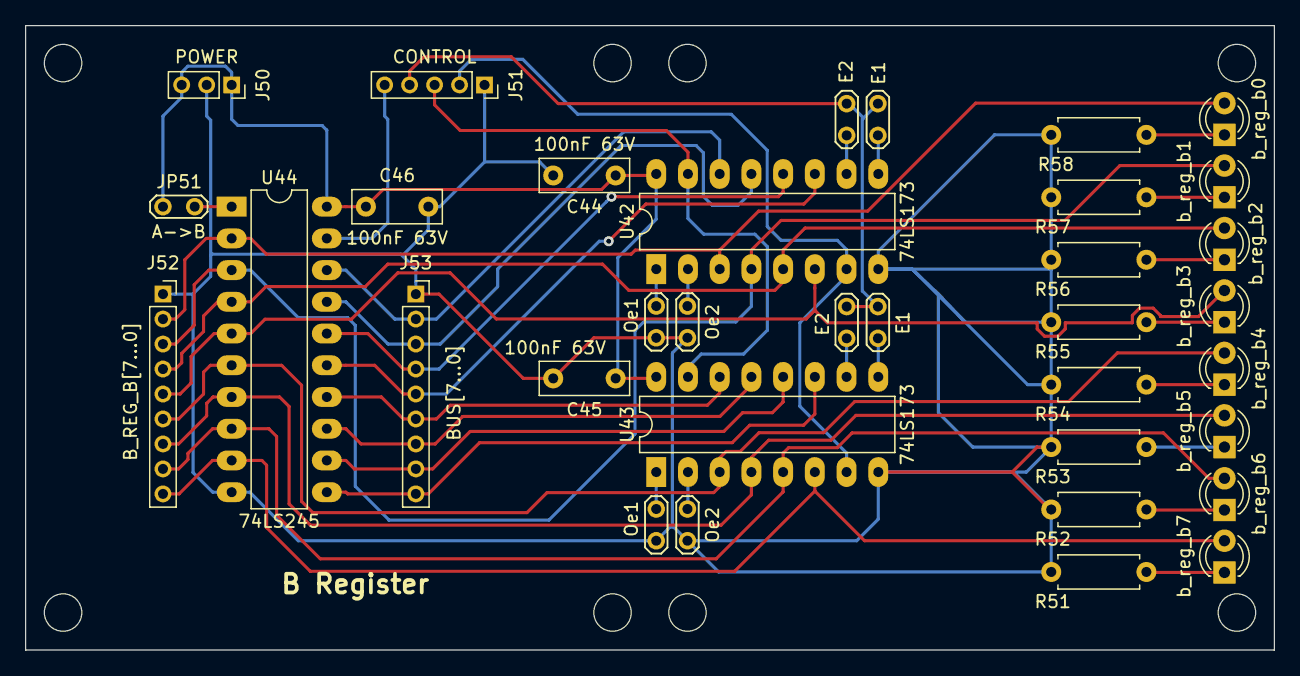
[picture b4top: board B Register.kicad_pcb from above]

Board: 2 copper layers, 100.0 x 50.0 mm, 35 parts (0 on the bottom side), 39 nets.

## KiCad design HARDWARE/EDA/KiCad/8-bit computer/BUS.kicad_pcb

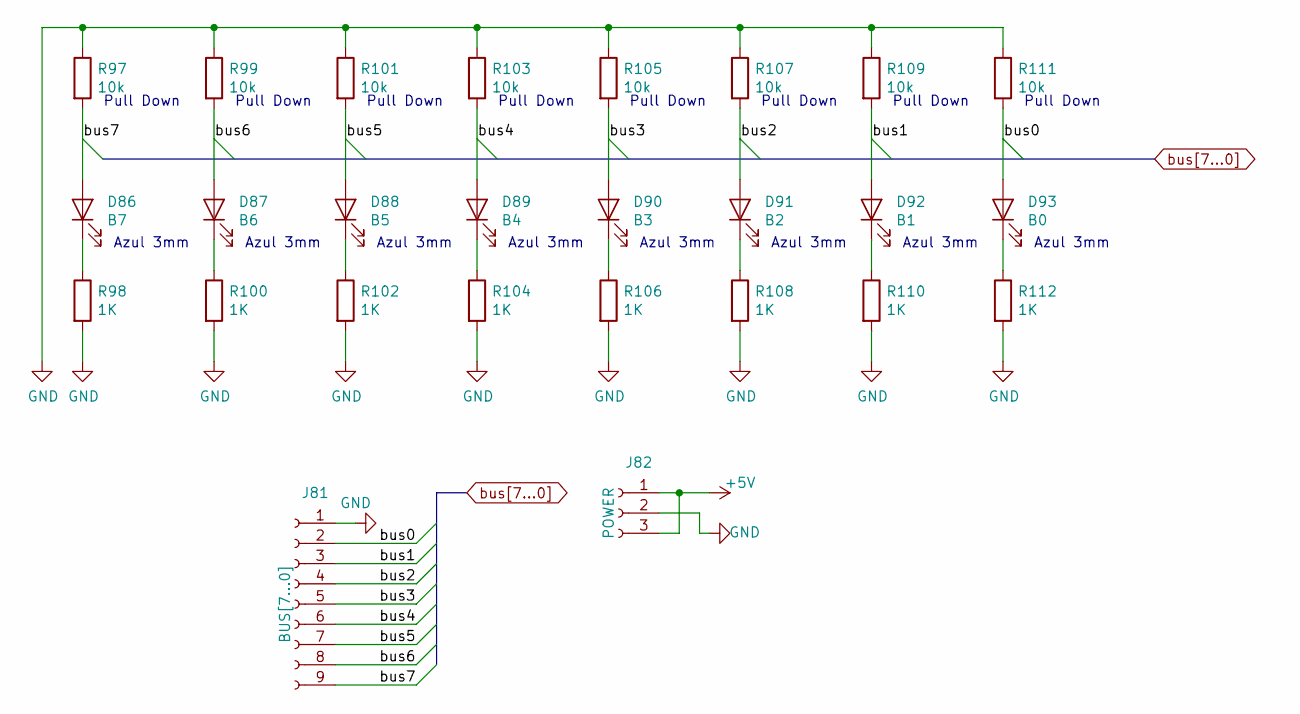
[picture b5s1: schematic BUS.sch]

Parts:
D86: B7; LED_D3.0mm_Clear
D87: B6; LED_D3.0mm_Clear
D88: B5; LED_D3.0mm_Clear
D89: B4; LED_D3.0mm_Clear
D90: B3; LED_D3.0mm_Clear
D91: B2; LED_D3.0mm_Clear
D92: B1; LED_D3.0mm_Clear
D93: B0; LED_D3.0mm_Clear
J81: BUS[7...0]; PinSocket_1x09_P2.00mm_Vertical
J82: POWER; PinSocket_1x03_P2.00mm_Vertical
R97, R99, R101, R103, R105, R107, R109, R111: 10k; R_Axial_DIN0207_L6.3mm_D2.5mm_P7.62mm_Horizontal
R98, R100, R102, R104, R106, R108, R110, R112: 1K; R_Axial_DIN0207_L6.3mm_D2.5mm_P7.62mm_Horizontal

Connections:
+5V: J82.1, J82.3
GND: J81.1, J82.2, R97.1, R98.2, R99.1, R100.2, R101.1, R102.2, R103.1, R104.2, R105.1, R106.2, R107.1, R108.2, R109.1, R110.2, R111.1, R112.2
unnamed: D86.1 (K), R98.1
unnamed: D87.1 (K), R100.1
unnamed: D88.1 (K), R102.1
unnamed: D89.1 (K), R104.1
unnamed: D90.1 (K), R106.1
unnamed: D91.1 (K), R108.1
unnamed: D92.1 (K), R110.1
unnamed: D93.1 (K), R112.1
bus0: D93.2 (A), J81.2, R111.2
bus1: D92.2 (A), J81.3, R109.2
bus2: D91.2 (A), J81.4, R107.2
bus3: D90.2 (A), J81.5, R105.2
bus4: D89.2 (A), J81.6, R103.2
bus5: D88.2 (A), J81.7, R101.2
bus6: D87.2 (A), J81.8, R99.2
bus7: D86.2 (A), J81.9, R97.2

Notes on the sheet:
Azul 3mm
Pull Down

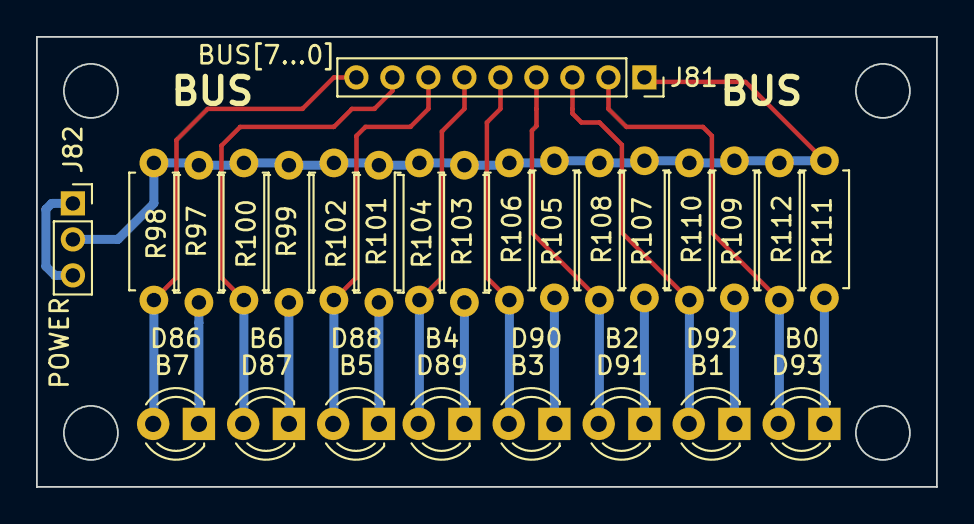
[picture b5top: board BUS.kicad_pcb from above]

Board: 2 copper layers, 50.0 x 25.0 mm, 26 parts (0 on the bottom side), 18 nets.
